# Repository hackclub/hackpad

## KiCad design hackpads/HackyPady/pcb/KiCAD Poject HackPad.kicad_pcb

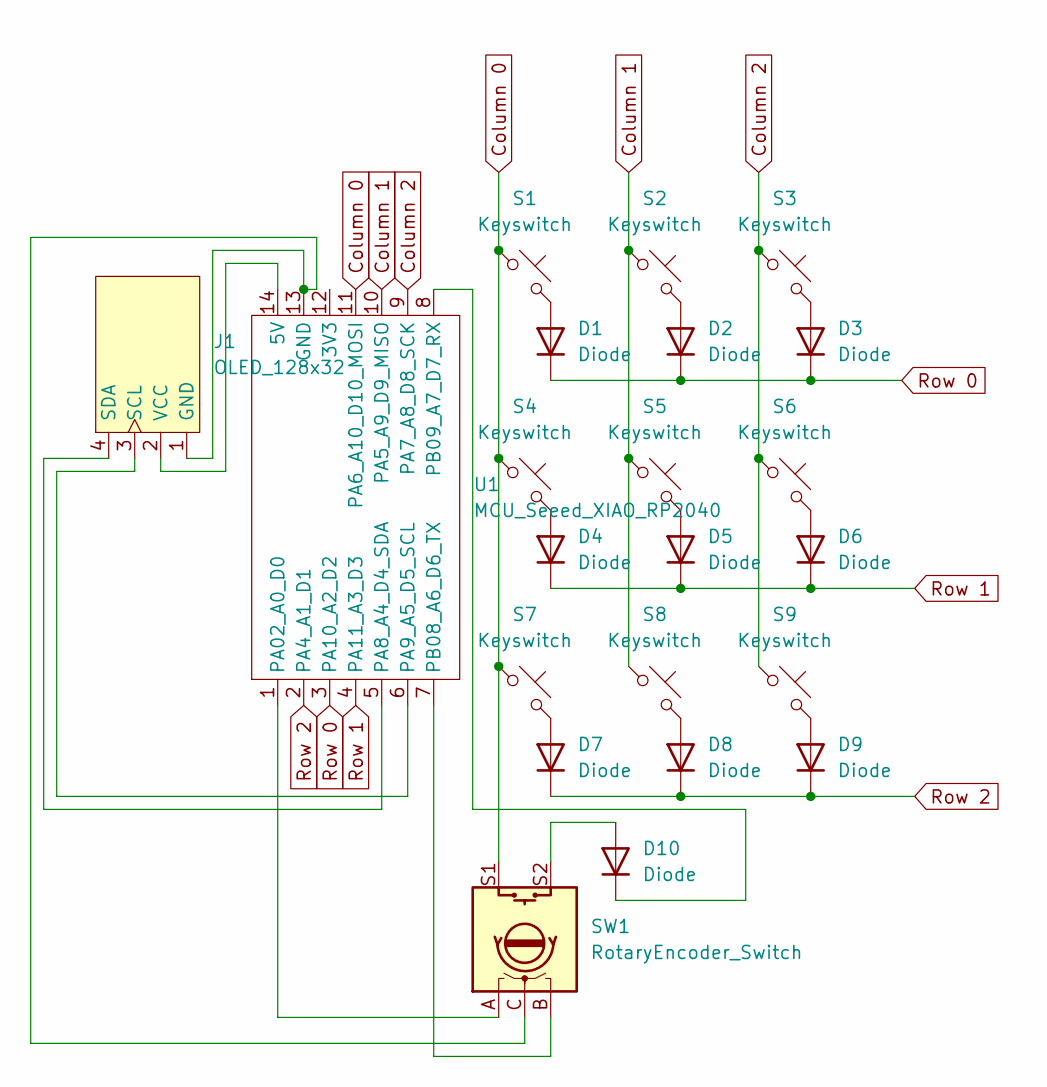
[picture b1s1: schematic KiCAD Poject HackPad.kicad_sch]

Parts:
D1, D2, D3, D4, D5, D6, D7, D8, D9, D10: Diode; Diode_DO-35
J1: OLED_128x32
S1, S2, S3, S4, S5, S6, S7, S8, S9: Keyswitch; SW_Cherry_MX_1.00u_PCB
SW1: RotaryEncoder_Switch; RotaryEncoder_Alps_EC11E-Switch_Vertical_H20mm
U1: MCU_Seeed_XIAO_RP2040; Seeed_XIAO_RP2040

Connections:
Column 0: S1.1, S4.1, S7.1, SW1.S1, U1.11 (PA6_A10_D10_MOSI)
Column 1: S2.1, S5.1, S8.1, U1.10 (PA5_A9_D9_MISO)
Column 2: S3.1, S6.1, S9.1, U1.9 (PA7_A8_D8_SCK)
unnamed: D1.2 (A), S1.2
unnamed: D2.2 (A), S2.2
unnamed: D3.2 (A), S3.2
unnamed: D4.2 (A), S4.2
unnamed: D5.2 (A), S5.2
unnamed: D6.2 (A), S6.2
unnamed: D7.2 (A), S7.2
unnamed: D8.2 (A), S8.2
unnamed: D9.2 (A), S9.2
unnamed: D10.2 (A), SW1.S2
unnamed: D10.1 (K), U1.8 (PB09_A7_D7_RX)
unnamed: J1.1 (GND), SW1.C, U1.13 (GND)
unnamed: J1.3 (SCL), U1.6 (PA9_A5_D5_SCL)
unnamed: J1.4 (SDA), U1.5 (PA8_A4_D4_SDA)
unnamed: J1.2 (VCC), U1.14 (5V)
unnamed: SW1.A, U1.1 (PA02_A0_D0)
unnamed: SW1.B, U1.7 (PB08_A6_D6_TX)
Row 0: D1.1 (K), D2.1 (K), D3.1 (K), U1.3 (PA10_A2_D2)
Row 1: D4.1 (K), D5.1 (K), D6.1 (K), U1.4 (PA11_A3_D3)
Row 2: D7.1 (K), D8.1 (K), D9.1 (K), U1.2 (PA4_A1_D1)

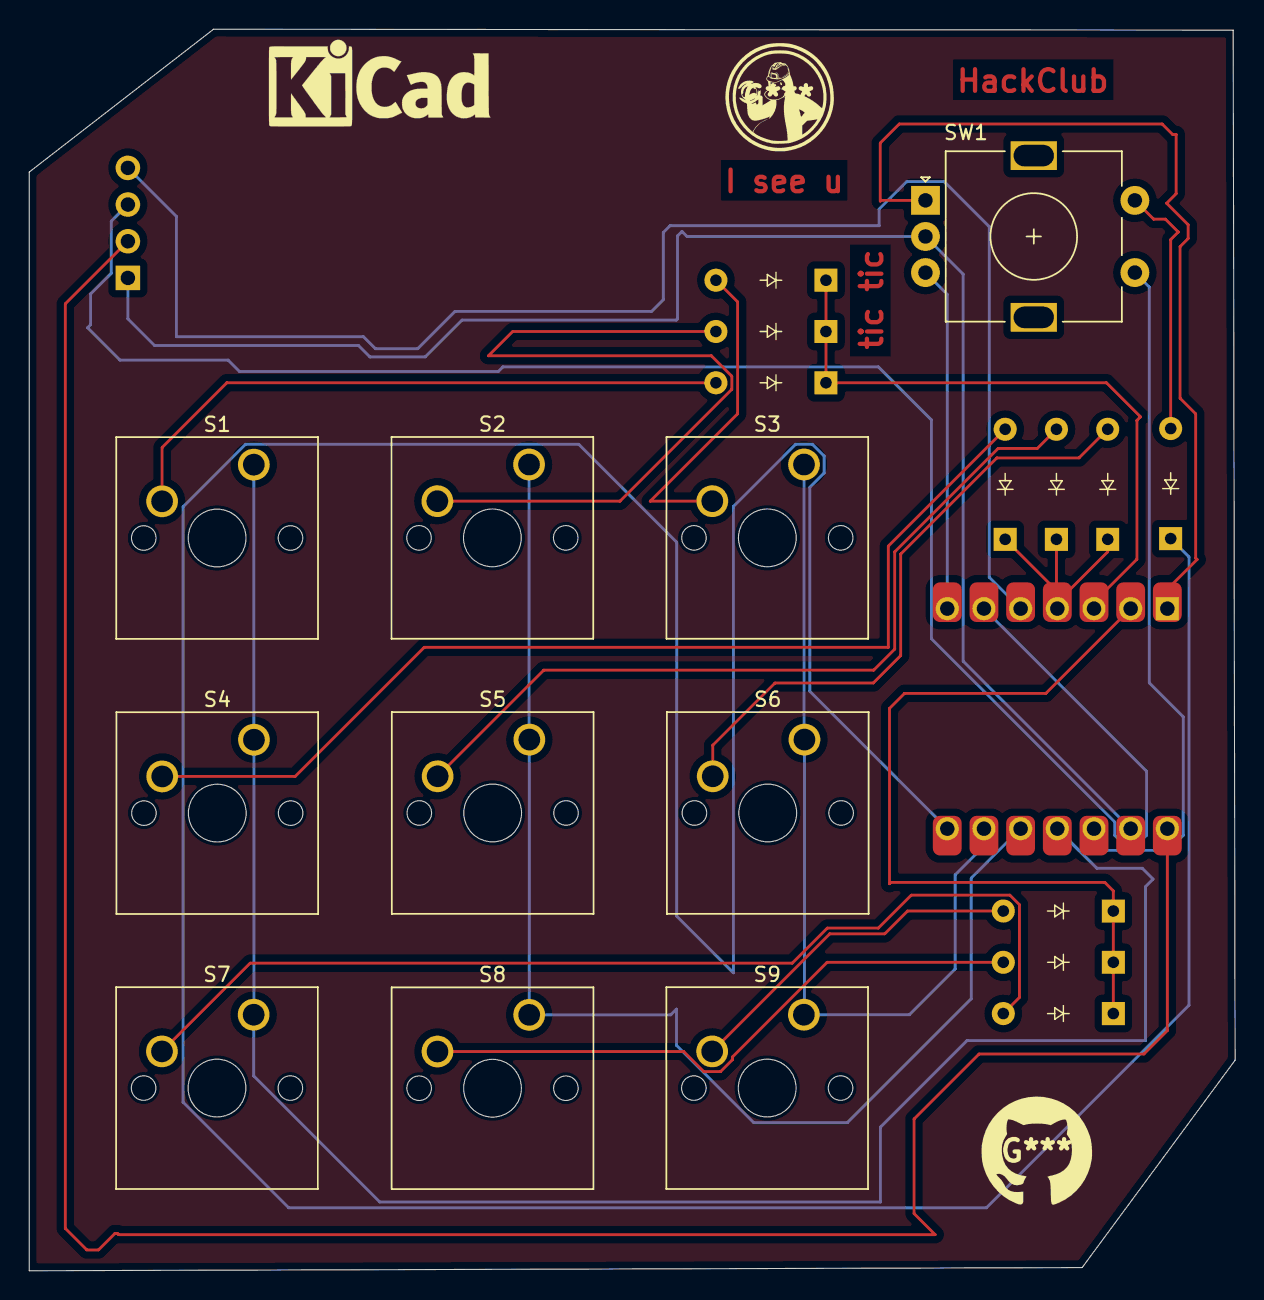
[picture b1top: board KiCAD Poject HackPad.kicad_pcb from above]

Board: 2 copper layers, 83.5 x 86.0 mm, 22 parts (0 on the bottom side), 23 nets.

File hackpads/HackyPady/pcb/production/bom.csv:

Designator,Footprint,Quantity,Value,LCSC Part #
"D1, D10, D2, D3, D4, D5, D6, D7, D8, D9",Diode_DO-35,10,Diode,
J1,OLED_128x32,1,OLED_128x32,
"S1, S2, S3, S4, S5, S6, S7, S8, S9",SW_Cherry_MX_1.00u_PCB,9,Keyswitch,
SW1,RotaryEncoder_Alps_EC11E-Switch_Vertical_H20mm,1,RotaryEncoder_Switch,
U1,Seeed_XIAO_RP2040,1,MCU_Seeed_XIAO_RP2040,

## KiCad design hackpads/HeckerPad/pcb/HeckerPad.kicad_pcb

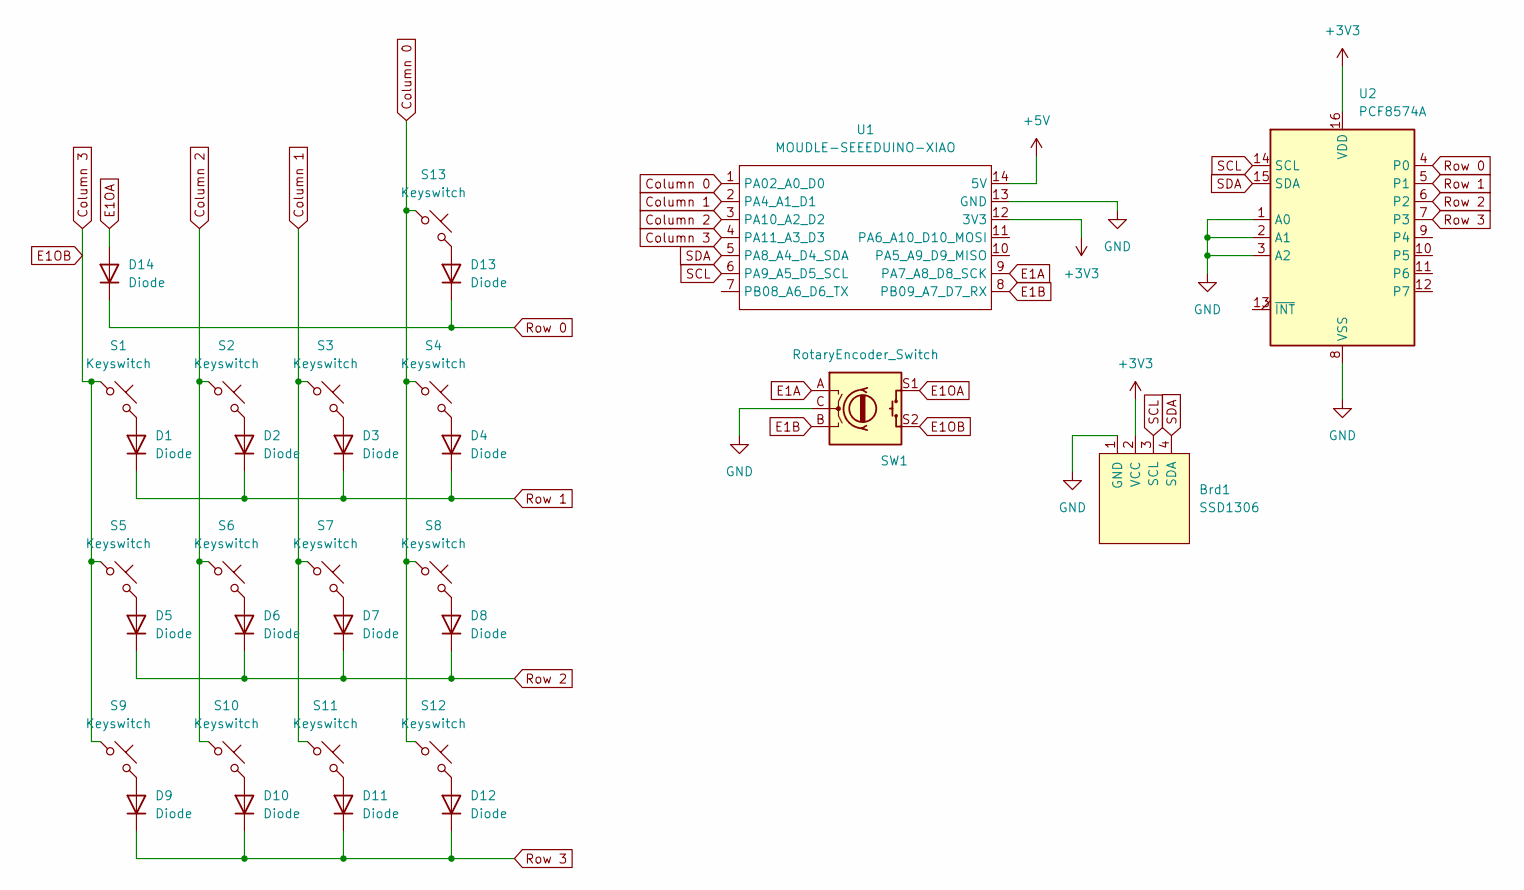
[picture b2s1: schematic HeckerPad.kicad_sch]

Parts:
Brd1: SSD1306; OLED_128x32
D1, D2, D3, D4, D5, D6, D7, D8, D9, D10, D11, D12, D13, D14: Diode; Diode_DO-35
S1, S2, S3, S4, S5, S6, S7, S8, S9, S10, S11, S12, S13: Keyswitch; SW_Cherry_MX_1.00u_PCB
SW1: RotaryEncoder_Switch; RotaryEncoder_Alps_EC11E-Switch_Vertical_H20mm
U1: MOUDLE-SEEEDUINO-XIAO; XIAO-Generic-Hybrid-14P-2.54-21X17.8MM
U2: PCF8574A; N16

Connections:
+3V3: Brd1.2 (VCC), U1.12 (3V3), U2.16 (VDD)
+5V: U1.14 (5V)
Column 0: S4.1, S8.1, S12.1, S13.1, U1.1 (PA02_A0_D0)
Column 1: S3.1, S7.1, S11.1, U1.2 (PA4_A1_D1)
Column 2: S2.1, S6.1, S10.1, U1.3 (PA10_A2_D2)
Column 3: S1.1, S5.1, S9.1, SW1.S2, U1.4 (PA11_A3_D3)
E1A: SW1.A, U1.9 (PA7_A8_D8_SCK)
E1B: SW1.B, U1.8 (PB09_A7_D7_RX)
E1OA: D14.2 (A), SW1.S1
GND: Brd1.1 (GND), SW1.C, U1.13 (GND), U2.1 (A0), U2.2 (A1), U2.3 (A2), U2.8 (VSS)
unnamed: D1.2 (A), S1.2
unnamed: D2.2 (A), S2.2
unnamed: D3.2 (A), S3.2
unnamed: D4.2 (A), S4.2
unnamed: D5.2 (A), S5.2
unnamed: D6.2 (A), S6.2
unnamed: D7.2 (A), S7.2
unnamed: D8.2 (A), S8.2
unnamed: D9.2 (A), S9.2
unnamed: D10.2 (A), S10.2
unnamed: D11.2 (A), S11.2
unnamed: D12.2 (A), S12.2
unnamed: D13.2 (A), S13.2
Row 0: D13.1 (K), D14.1 (K), U2.4 (P0)
Row 1: D1.1 (K), D2.1 (K), D3.1 (K), D4.1 (K), U2.5 (P1)
Row 2: D5.1 (K), D6.1 (K), D7.1 (K), D8.1 (K), U2.6 (P2)
Row 3: D9.1 (K), D10.1 (K), D11.1 (K), D12.1 (K), U2.7 (P3)
SCL: Brd1.3 (SCL), U1.6 (PA9_A5_D5_SCL), U2.14 (SCL)
SDA: Brd1.4 (SDA), U1.5 (PA8_A4_D4_SDA), U2.15 (SDA)

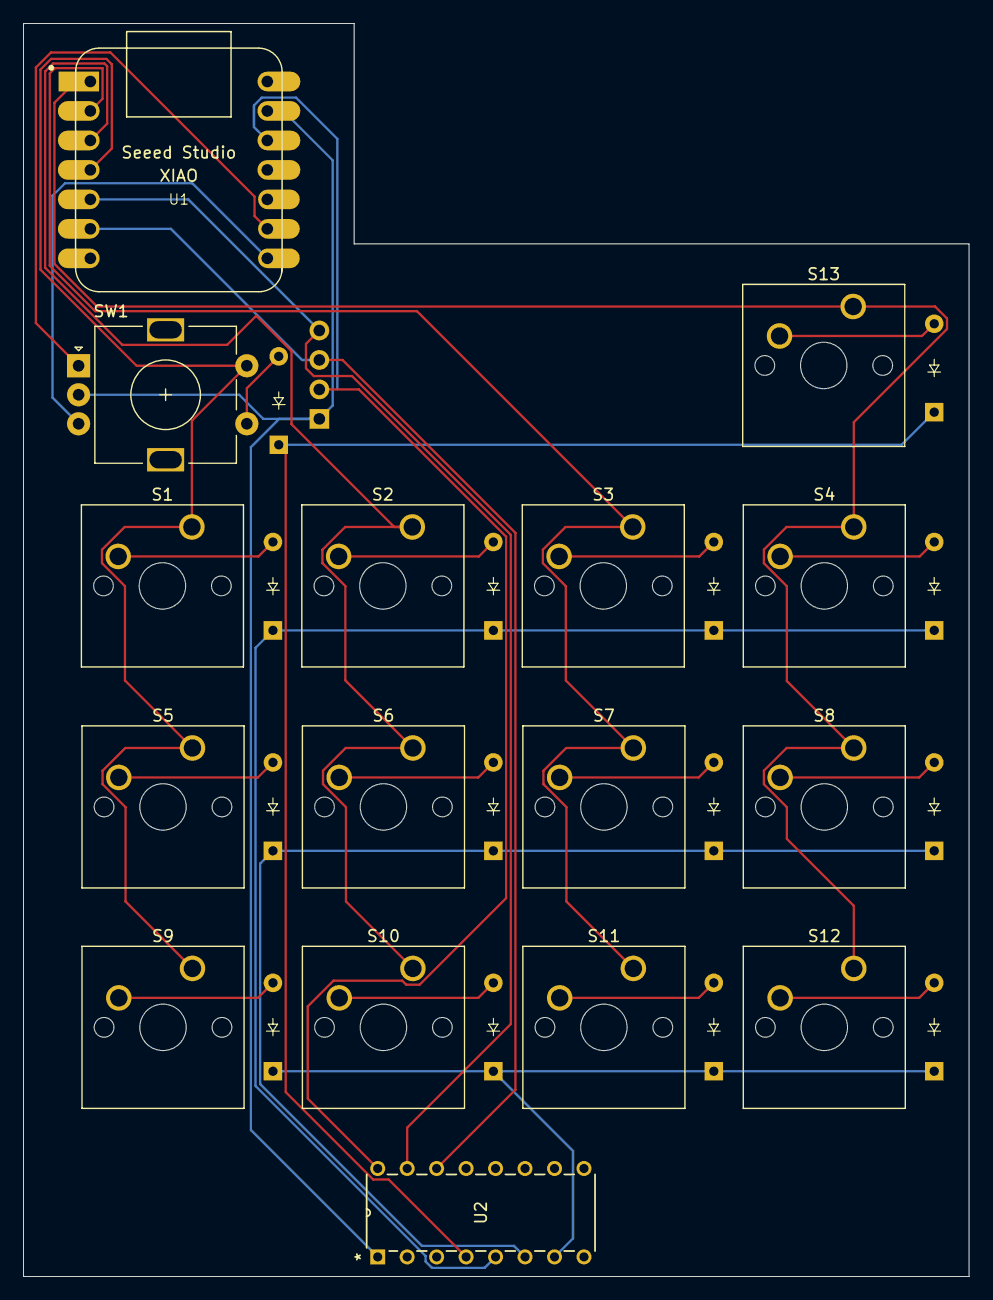
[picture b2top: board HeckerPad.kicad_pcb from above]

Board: 2 copper layers, 81.5 x 108.0 mm, 31 parts (0 on the bottom side), 28 nets.

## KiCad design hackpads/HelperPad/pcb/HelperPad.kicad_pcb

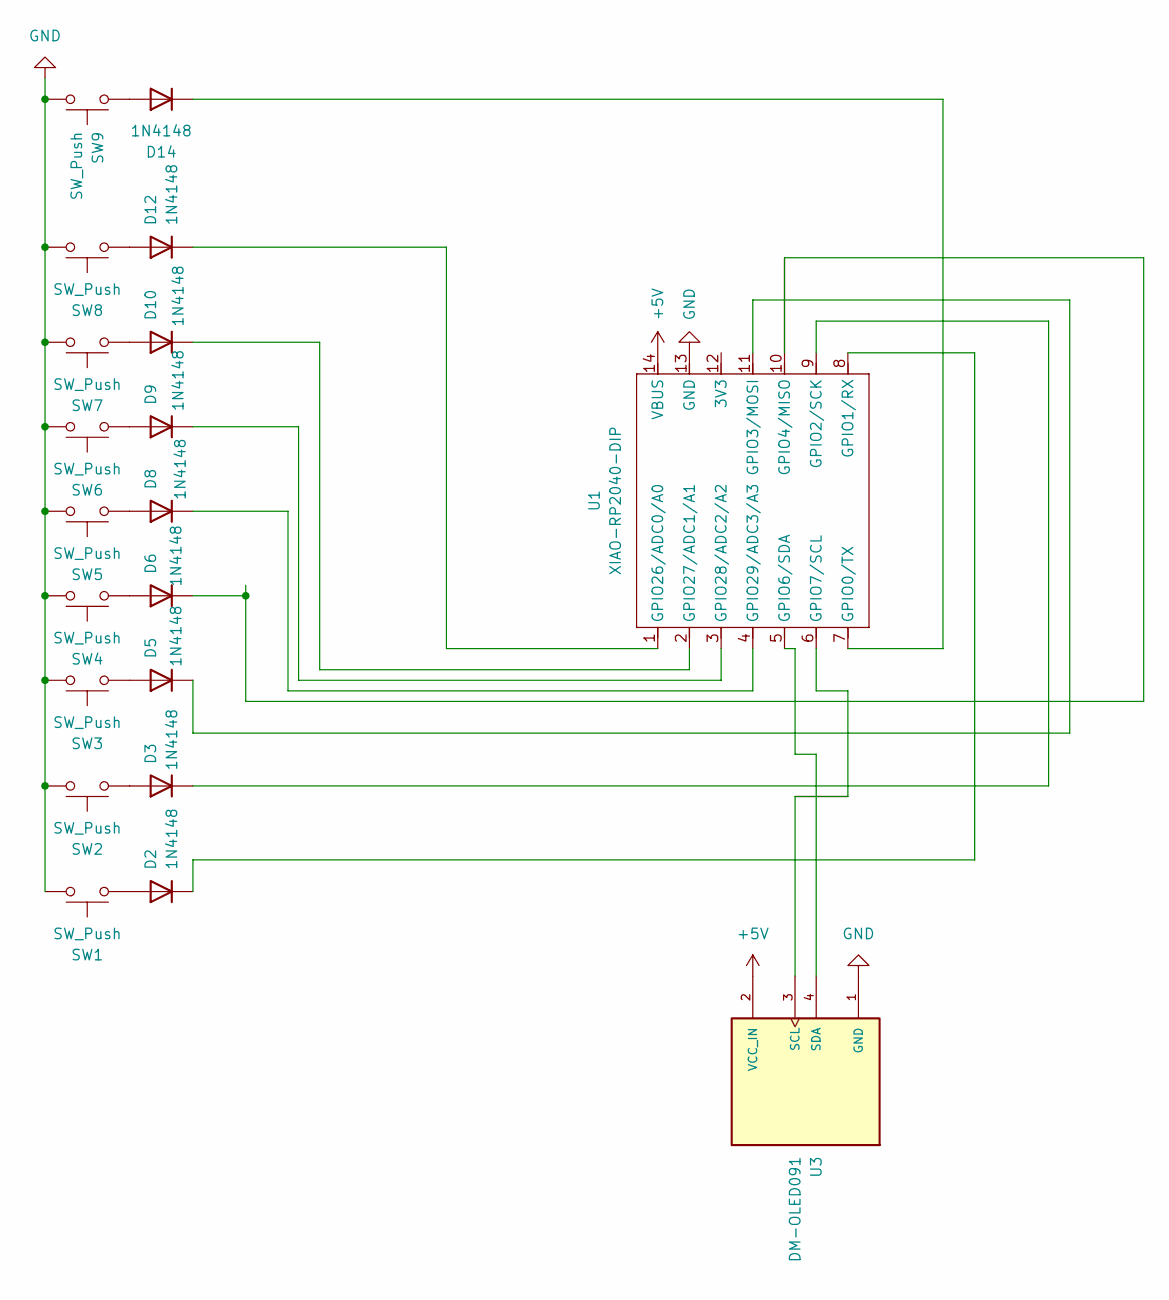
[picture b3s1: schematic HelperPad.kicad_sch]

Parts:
D2, D3, D5, D6, D8, D9, D10, D12, D14: 1N4148; D_DO-35_SOD27_P7.62mm_Horizontal
SW1, SW2, SW3, SW4, SW5, SW6, SW7, SW8, SW9: SW_Push; SW_Cherry_MX_1.00u_PCB
U1: XIAO-RP2040-DIP
U3: DM-OLED091; SSD1306-0.91-OLED-4pin-128x32; PARTREV 2018-09-10

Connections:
+5V: U1.14 (VBUS), U3.2 (VCC_IN)
GND: SW1.2, SW2.2, SW3.2, SW4.2, SW5.2, SW6.2, SW7.2, SW8.2, SW9.2, U1.13 (GND), U3.1 (GND)
unnamed: D2.2 (A), SW1.1
unnamed: D2.1 (K), U1.8 (GPIO1/RX)
unnamed: D3.2 (A), SW2.1
unnamed: D3.1 (K), U1.9 (GPIO2/SCK)
unnamed: D5.2 (A), SW3.1
unnamed: D5.1 (K), U1.11 (GPIO3/MOSI)
unnamed: D6.2 (A), SW4.1
unnamed: D6.1 (K), U1.10 (GPIO4/MISO)
unnamed: D8.2 (A), SW5.1
unnamed: D8.1 (K), U1.4 (GPIO29/ADC3/A3)
unnamed: D9.2 (A), SW6.1
unnamed: D9.1 (K), U1.3 (GPIO28/ADC2/A2)
unnamed: D10.2 (A), SW7.1
unnamed: D10.1 (K), U1.2 (GPIO27/ADC1/A1)
unnamed: D12.2 (A), SW8.1
unnamed: D12.1 (K), U1.1 (GPIO26/ADC0/A0)
unnamed: D14.2 (A), SW9.1
unnamed: D14.1 (K), U1.7 (GPIO0/TX)
unnamed: U1.5 (GPIO6/SDA), U3.4 (SDA)
unnamed: U1.6 (GPIO7/SCL), U3.3 (SCL)

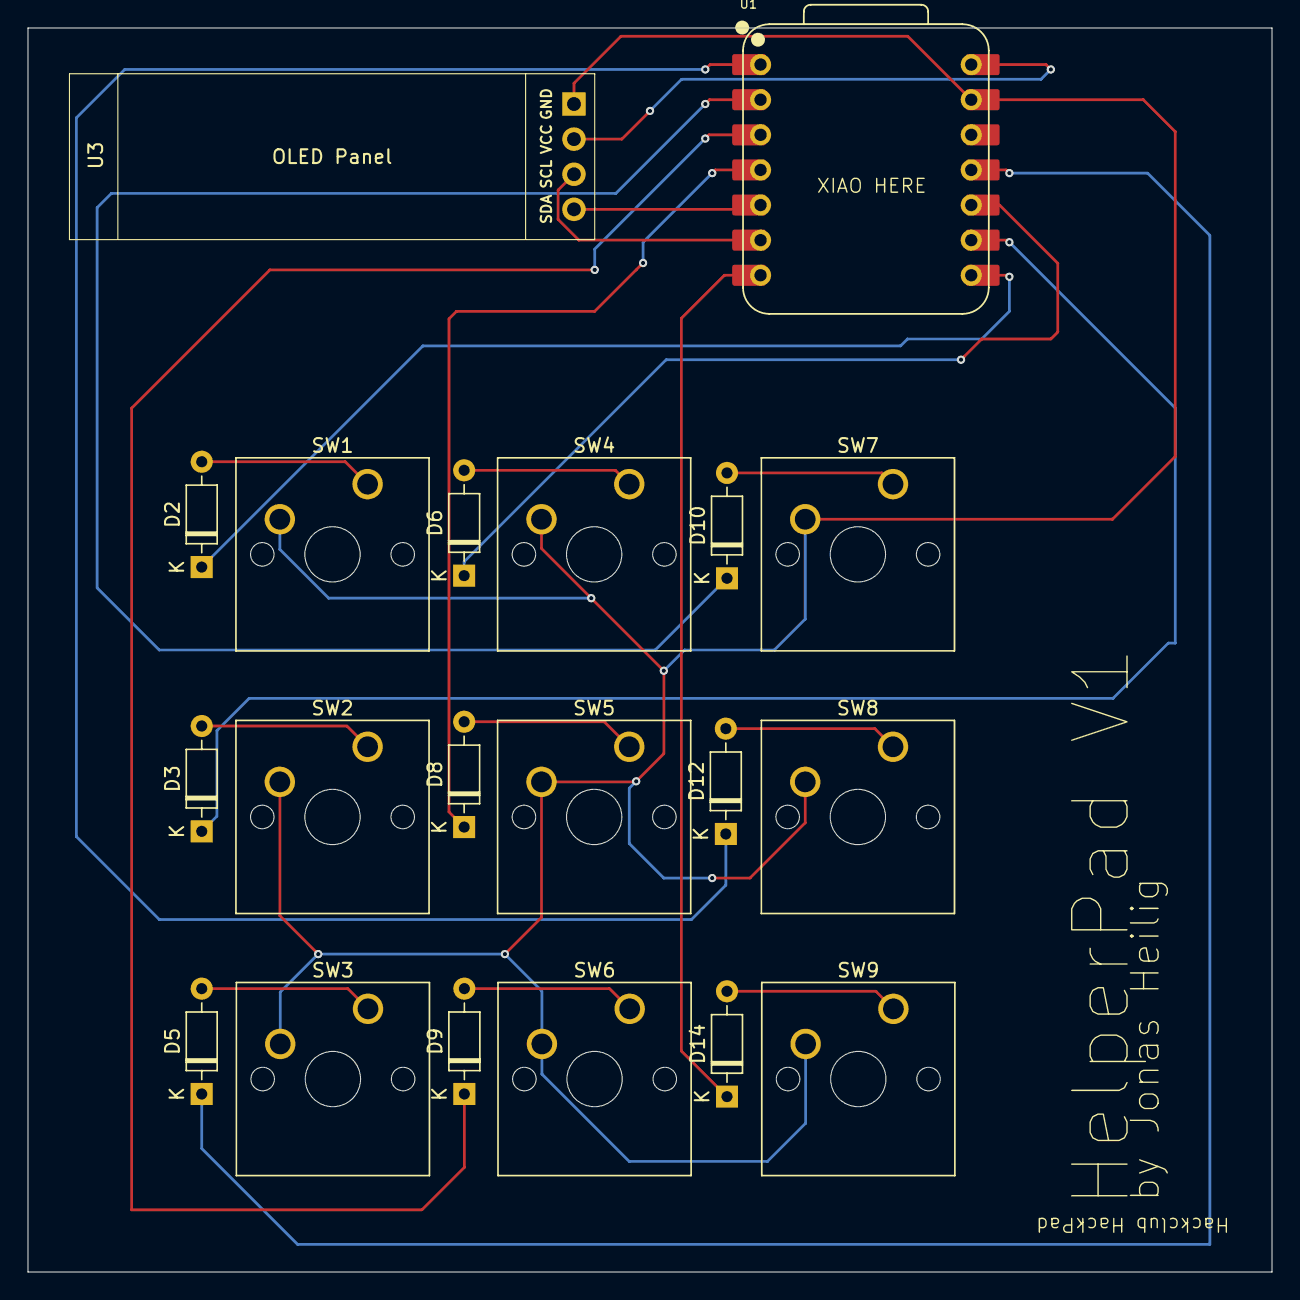
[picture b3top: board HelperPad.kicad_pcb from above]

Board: 2 copper layers, 90.0 x 90.0 mm, 20 parts (0 on the bottom side), 22 nets.

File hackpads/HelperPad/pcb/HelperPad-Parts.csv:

"#","Value","Reference","Footprint","Qty","DNP"
"1","1N4148","D2,D3,D5,D6,D8,D9,D10,D12,D14","Diode_THT:D_DO-35_SOD27_P7.62mm_Horizontal","9",""
"2","SW_Push","SW1,SW2,SW3,SW4,SW5,SW6,SW7,SW8,SW9","Button_Switch_Keyboard:SW_Cherry_MX_1.00u_PCB","9",""
"3","XIAO-RP2040-DIP","U1","OPL:XIAO-RP2040-DIP","1",""
"4","DM-OLED091","U3","OLED_096:SSD1306-0.91-OLED-4pin-128x32","1",""

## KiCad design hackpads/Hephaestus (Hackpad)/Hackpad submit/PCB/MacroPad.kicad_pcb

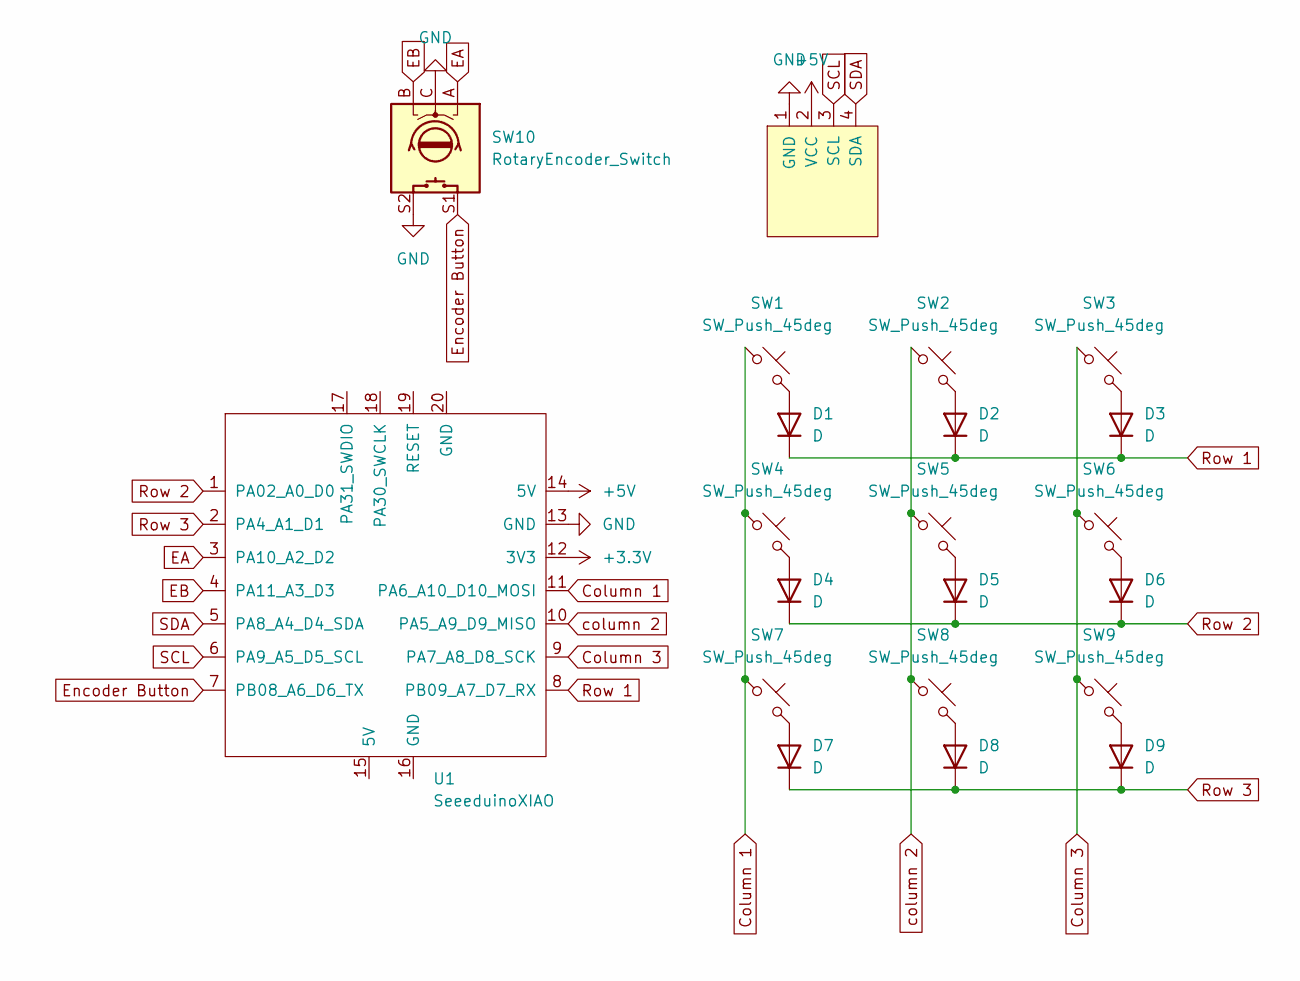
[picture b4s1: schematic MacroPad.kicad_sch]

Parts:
Brd1: SSD1306; 128x64OLED
D1, D2, D3, D4, D5, D6, D7, D8, D9: D; D_DO-35_SOD27_P7.62mm_Horizontal
SW1, SW2, SW3, SW4, SW5, SW6, SW7, SW8, SW9: SW_Push_45deg; SW_Cherry_MX_1.00u_PCB
SW10: RotaryEncoder_Switch; RotaryEncoder_Alps_EC11E-Switch_Vertical_H20mm
U1: SeeeduinoXIAO; XIAO-SAMD21-DIP

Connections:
+3.3V: U1.12 (3V3)
+5V: Brd1.2 (VCC), U1.14 (5V)
Column 1: SW1.1, SW4.1, SW7.1, U1.11 (PA6_A10_D10_MOSI)
Column 3: SW3.1, SW6.1, SW9.1, U1.9 (PA7_A8_D8_SCK)
EA: SW10.A, U1.3 (PA10_A2_D2)
EB: SW10.B, U1.4 (PA11_A3_D3)
Encoder Button: SW10.S1, U1.7 (PB08_A6_D6_TX)
GND: Brd1.1 (GND), SW10.C, SW10.S2, U1.13 (GND)
unnamed: D1.2 (A), SW1.2
unnamed: D2.2 (A), SW2.2
unnamed: D3.2 (A), SW3.2
unnamed: D4.2 (A), SW4.2
unnamed: D5.2 (A), SW5.2
unnamed: D6.2 (A), SW6.2
unnamed: D7.2 (A), SW7.2
unnamed: D8.2 (A), SW8.2
unnamed: D9.2 (A), SW9.2
Row 1: D1.1 (K), D2.1 (K), D3.1 (K), U1.8 (PB09_A7_D7_RX)
Row 2: D4.1 (K), D5.1 (K), D6.1 (K), U1.1 (PA02_A0_D0)
Row 3: D7.1 (K), D8.1 (K), D9.1 (K), U1.2 (PA4_A1_D1)
SCL: Brd1.3 (SCL), U1.6 (PA9_A5_D5_SCL)
SDA: Brd1.4 (SDA), U1.5 (PA8_A4_D4_SDA)
column 2: SW2.1, SW5.1, SW8.1, U1.10 (PA5_A9_D9_MISO)

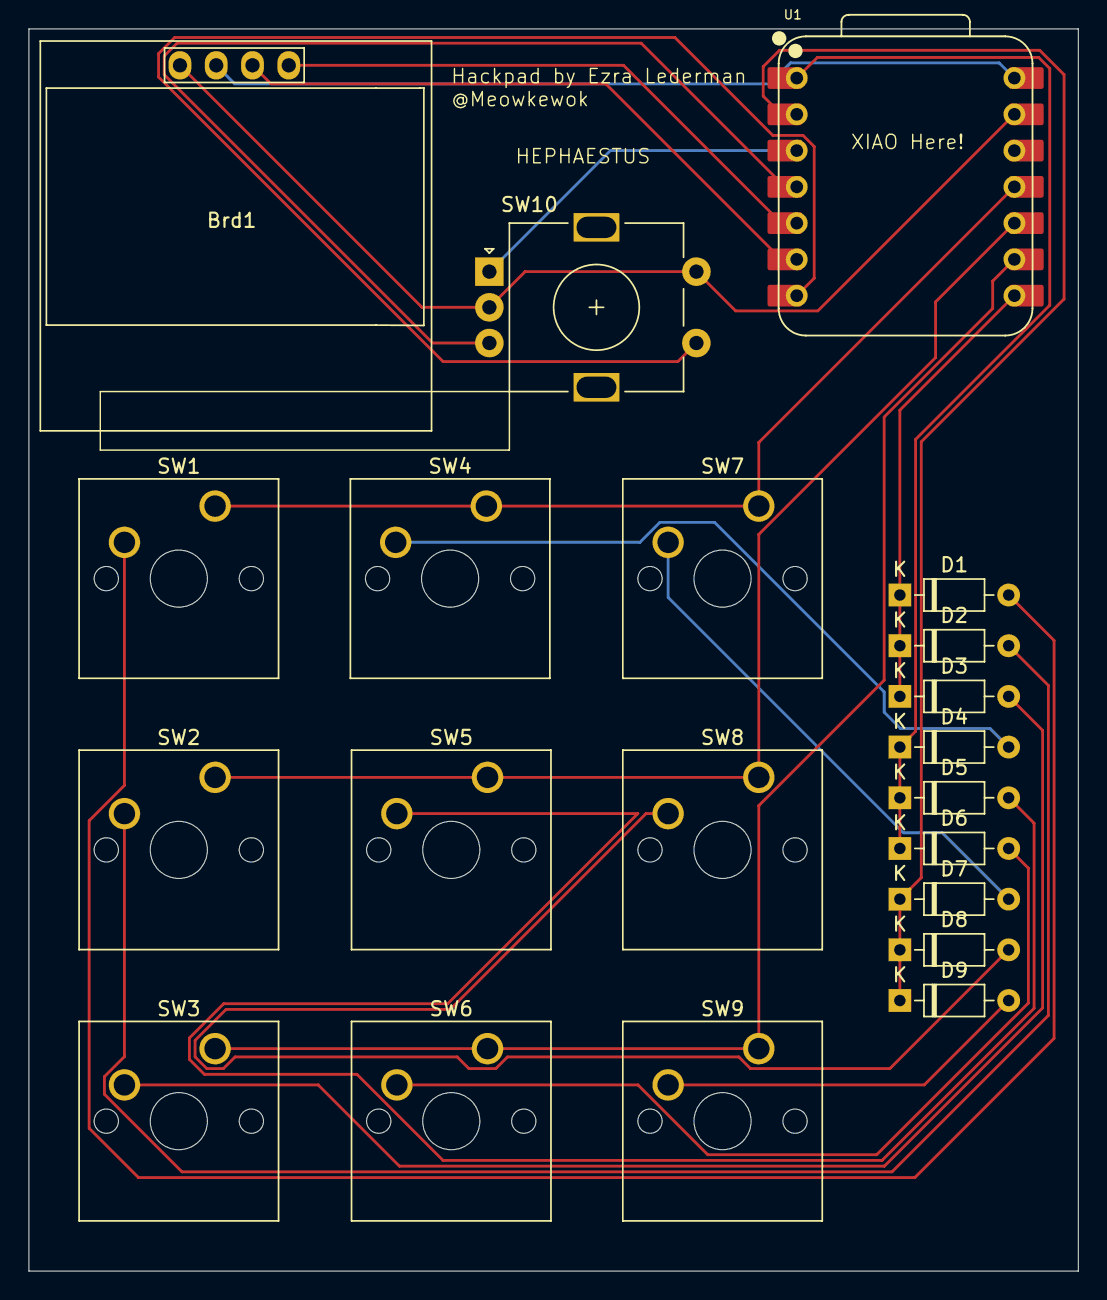
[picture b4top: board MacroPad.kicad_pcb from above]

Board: 2 copper layers, 73.5 x 87.0 mm, 21 parts (0 on the bottom side), 22 nets.

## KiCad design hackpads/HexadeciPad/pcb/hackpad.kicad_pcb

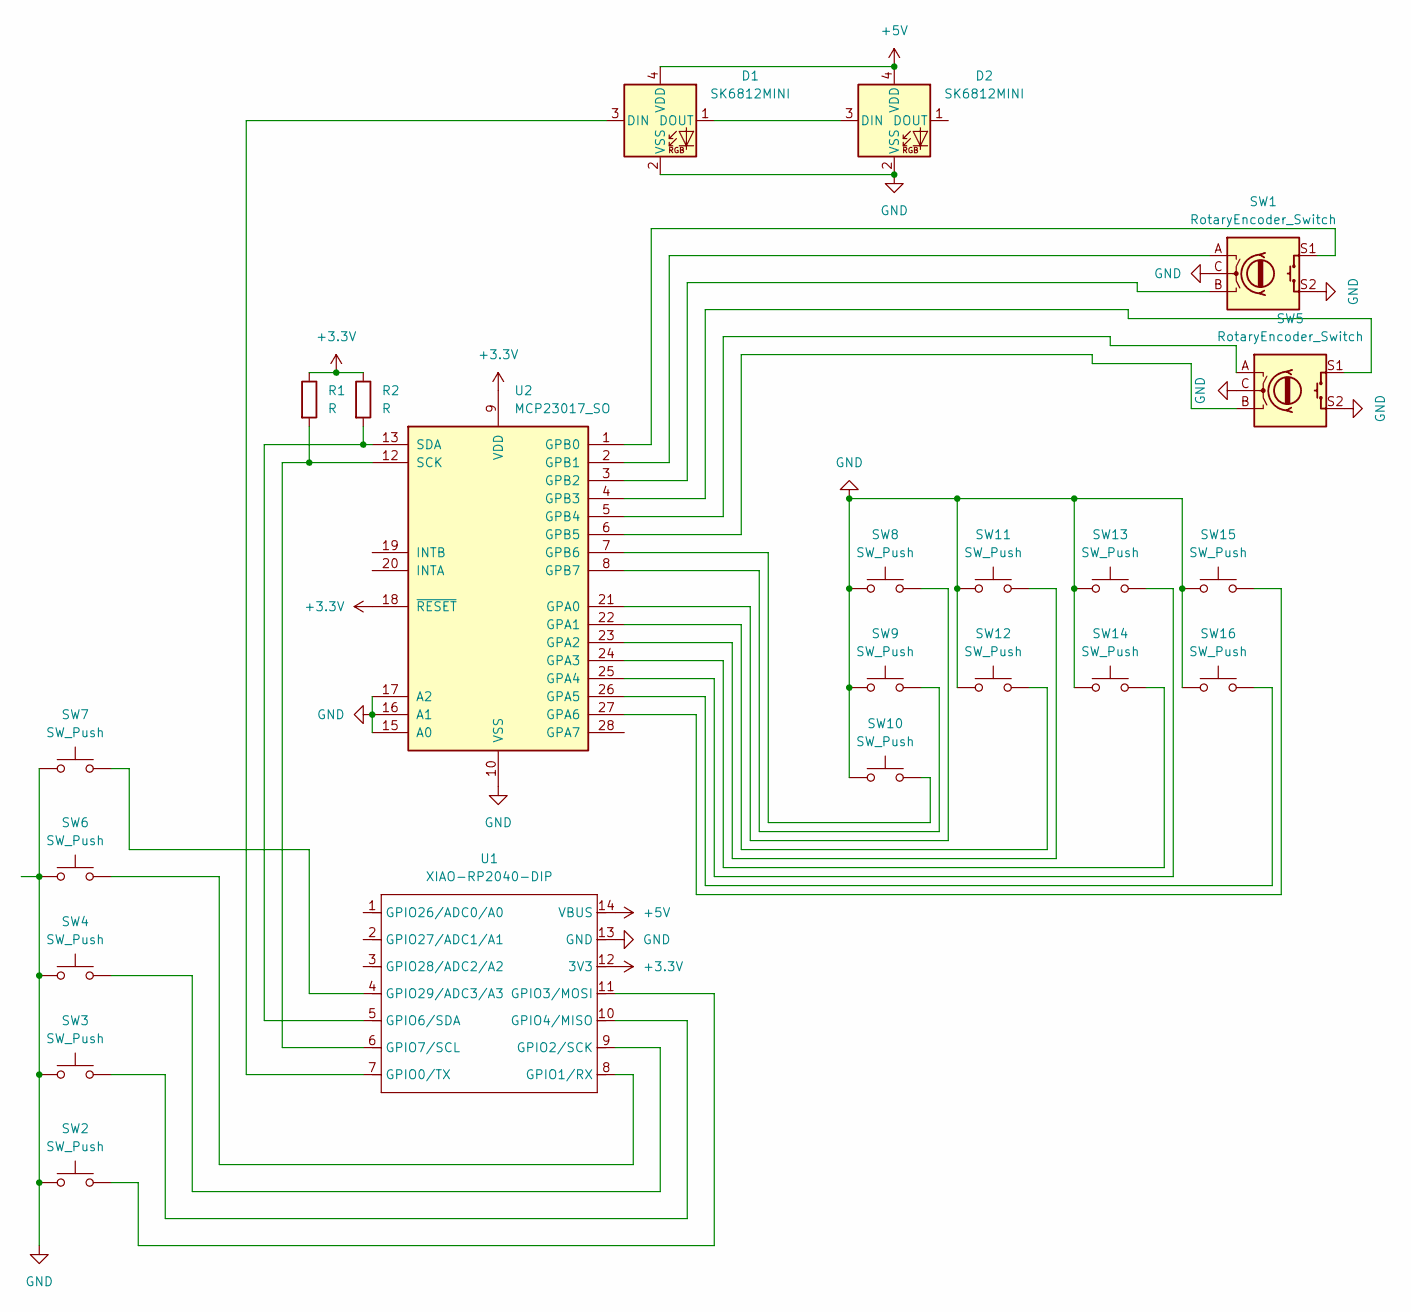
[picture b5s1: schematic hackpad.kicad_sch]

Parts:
D1, D2: SK6812MINI; LED_SK6812MINI_PLCC4_3.5x3.5mm_P1.75mm
R1, R2: R; R_Axial_DIN0204_L3.6mm_D1.6mm_P7.62mm_Horizontal
SW1, SW5: RotaryEncoder_Switch; RotaryEncoder_Alps_EC11E-Switch_Vertical_H20mm
SW2, SW3, SW4, SW6, SW7, SW8, SW9, SW10, SW11, SW12, SW13, SW14, SW15, SW16: SW_Push; SW_Cherry_MX_1.00u_PCB
U1: XIAO-RP2040-DIP
U2: MCP23017_SO; SOIC-28W_7.5x17.9mm_P1.27mm

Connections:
+3.3V: R1.1, R2.1, U1.12 (3V3), U2.9 (VDD), U2.18 (~RESET)
+5V: D1.4 (VDD), D2.4 (VDD), U1.14 (VBUS)
GND: D1.2 (VSS), D2.2 (VSS), SW1.C, SW1.S2, SW2.1, SW3.1, SW4.1, SW5.C, SW5.S2, SW6.1, SW7.1, SW8.1, SW9.1, SW10.1, SW11.1, SW12.1, SW13.1, SW14.1, SW15.1, SW16.1, U1.13 (GND), U2.10 (VSS), U2.15 (A0), U2.16 (A1), U2.17 (A2)
unnamed: D1.3 (DIN), U1.7 (GPIO0/TX)
unnamed: D1.1 (DOUT), D2.3 (DIN)
unnamed: SW6.2, U1.8 (GPIO1/RX)
unnamed: SW4.2, U1.9 (GPIO2/SCK)
unnamed: SW2.2, U1.11 (GPIO3/MOSI)
unnamed: SW3.2, U1.10 (GPIO4/MISO)
unnamed: R2.2, U1.5 (GPIO6/SDA), U2.13 (SDA)
unnamed: R1.2, U1.6 (GPIO7/SCL), U2.12 (SCK)
unnamed: SW7.2, U1.4 (GPIO29/ADC3/A3)
unnamed: SW8.2, U2.21 (GPA0)
unnamed: SW12.2, U2.22 (GPA1)
unnamed: SW11.2, U2.23 (GPA2)
unnamed: SW14.2, U2.24 (GPA3)
unnamed: SW13.2, U2.25 (GPA4)
unnamed: SW16.2, U2.26 (GPA5)
unnamed: SW15.2, U2.27 (GPA6)
unnamed: SW1.S1, U2.1 (GPB0)
unnamed: SW1.A, U2.2 (GPB1)
unnamed: SW1.B, U2.3 (GPB2)
unnamed: SW5.S1, U2.4 (GPB3)
unnamed: SW5.A, U2.5 (GPB4)
unnamed: SW5.B, U2.6 (GPB5)
unnamed: SW10.2, U2.7 (GPB6)
unnamed: SW9.2, U2.8 (GPB7)

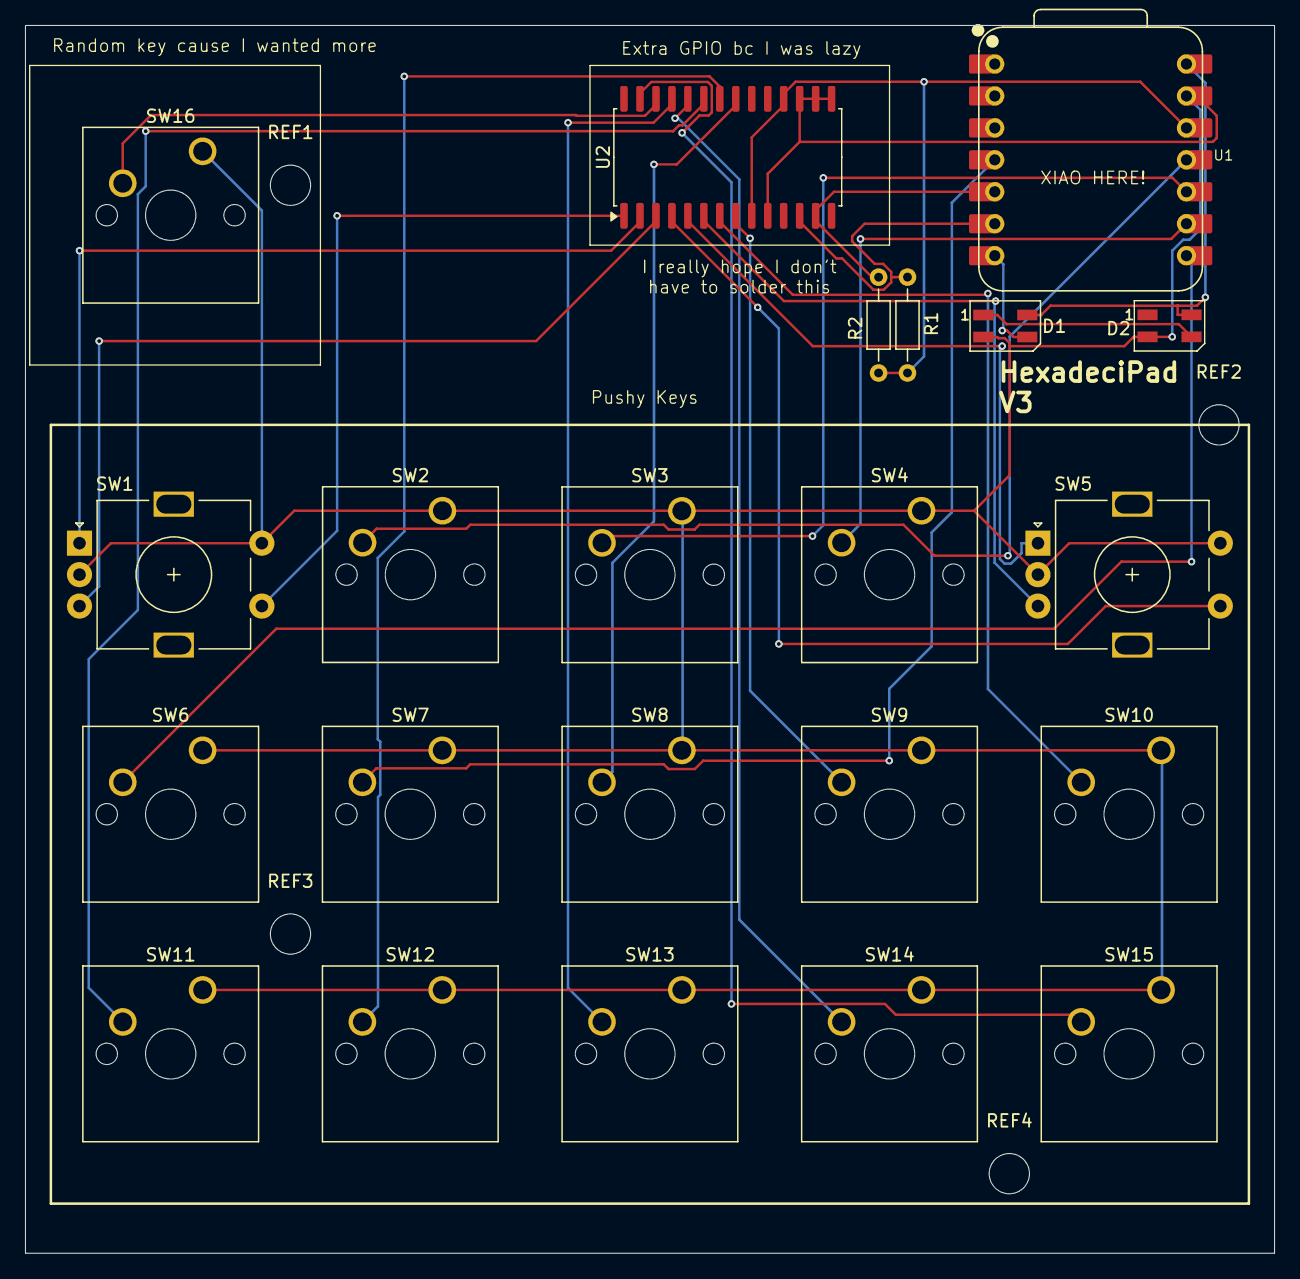
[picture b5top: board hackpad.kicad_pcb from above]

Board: 2 copper layers, 99.3 x 97.6 mm, 26 parts (0 on the bottom side), 27 nets.

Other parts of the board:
REF1, REF2, REF3, REF4: MountingHole_3.2mm_M3
